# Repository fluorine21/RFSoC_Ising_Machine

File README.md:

# RFSoC_Ising_Machine
An Ising Machine implementation using the RFSoC ZCU1275

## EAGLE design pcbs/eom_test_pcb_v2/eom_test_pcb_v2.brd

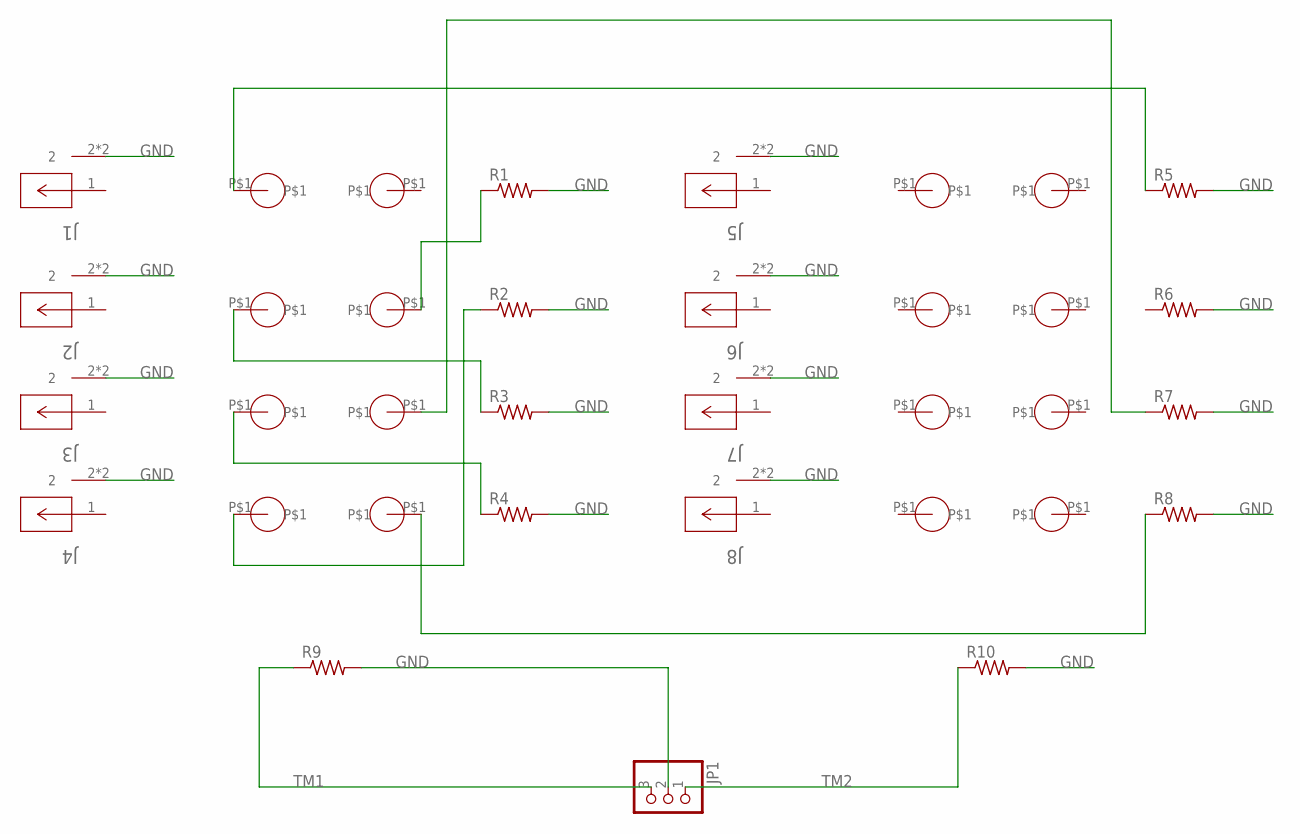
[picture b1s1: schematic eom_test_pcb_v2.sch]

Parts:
J1, J2, J3, J4, J5, J6, J7, J8: 142-0711-821; CONN_142-0711-821_CIN
JP1: PINHD-1X3; 1X03
R1, R2, R3, R4, R5, R6, R7, R8: R-US_M1206; M1206
R9, R10: R-US_R0402; R0402
U$1, U$2, U$3, U$4, U$5, U$6, U$7, U$8, U$9, U$10, U$11, U$12, U$13, U$14, U$15, U$16: SIGNAL_BONDING_DEVICE; SIGNAL_BONDING_PAD

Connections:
GND: J1.2, J1.3 (2), J2.2, J2.3 (2), J3.2, J3.3 (2), J4.2, J4.3 (2), J5.2, J5.3 (2), J6.2, J6.3 (2), J7.2, J7.3 (2), J8.2, J8.3 (2), JP1.2, R1.2, R2.2, R3.2, R4.2, R5.2, R6.2, R7.2, R8.2, R9.2, R10.2
unnamed: R7.1, U$6.P$1
unnamed: R8.1, U$8.P$1
unnamed: R3.1, U$3.P$1
unnamed: R4.1, U$5.P$1
unnamed: R5.1, U$1.P$1
unnamed: R2.1, U$7.P$1
unnamed: R1.1, U$4.P$1
unnamed: R6.1, U$2.P$1
unnamed: J5.1, U$12.P$1
unnamed: J6.1, U$11.P$1
unnamed: J4.1, U$16.P$1
unnamed: J3.1, U$15.P$1
unnamed: J7.1, U$14.P$1
unnamed: J2.1, U$10.P$1
unnamed: J8.1, U$9.P$1
unnamed: J1.1, U$13.P$1
TM1: JP1.3, R9.1
TM2: JP1.1, R10.1

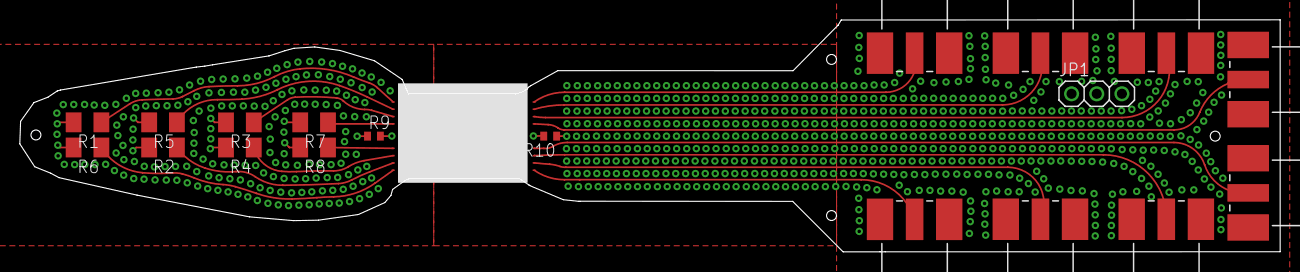
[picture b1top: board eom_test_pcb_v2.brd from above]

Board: 4 copper layers, 127.2 x 23.4 mm, 35 parts (0 on the bottom side), 19 nets.

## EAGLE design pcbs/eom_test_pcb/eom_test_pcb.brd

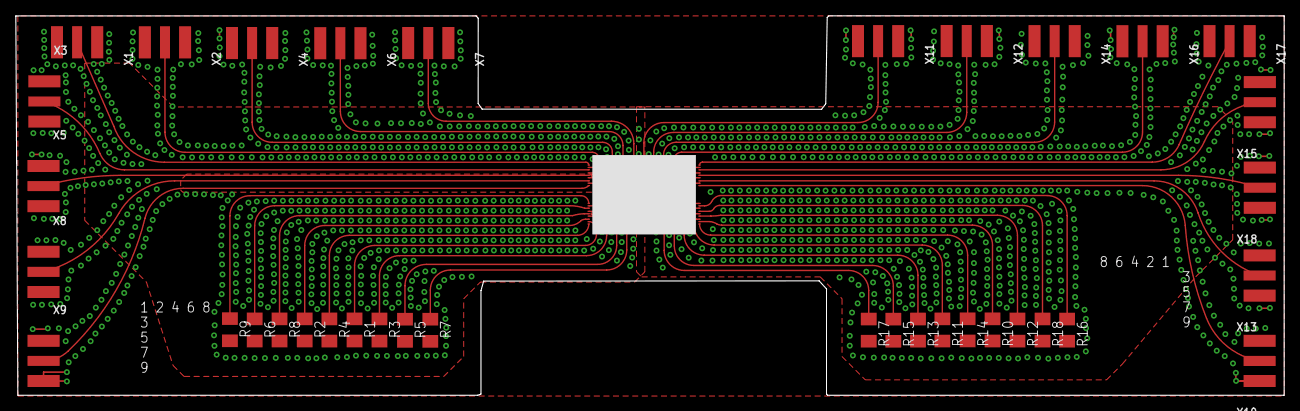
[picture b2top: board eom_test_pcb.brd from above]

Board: 4 copper layers, 160.3 x 47.9 mm, 72 parts (0 on the bottom side), 37 nets.

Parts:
R1, R2, R3, R4, R5, R6, R7, R8, R9, R10, R11, R12, R13, R14, R15, R16, R17, R18: M1206
U$1, U$2, U$3, U$4, U$5, U$6, U$7, U$8, U$9, U$10, U$11, U$12, U$13, U$14, U$15, U$16, U$17, U$18, U$19, U$20, U$21, U$22, U$23, U$24, U$25, U$26, U$27, U$28, U$29, U$30, U$31, U$32, U$33, U$34, U$35, U$36: SIGNAL_BONDING_DEVICE; SIGNAL_BONDING_PAD
X1, X2, X3, X4, X5, X6, X7, X8, X9, X10, X11, X12, X13, X14, X15, X16, X17, X18: SMA_EDGELAUNCH

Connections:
GND: R1.2, R2.2, R3.2, R4.2, R5.2, R6.2, R7.2, R8.2, R9.2, R10.2, R11.2, R12.2, R13.2, R14.2, R15.2, R16.2, R17.2, R18.2, X1.GND@1, X1.GND@2, X1.GND@3, X1.GND@4, X2.GND@1, X2.GND@2, X2.GND@3, X2.GND@4, X3.GND@1, X3.GND@2, X3.GND@3, X3.GND@4, X4.GND@1, X4.GND@2, X4.GND@3, X4.GND@4, X5.GND@1, X5.GND@2, X5.GND@3, X5.GND@4, X6.GND@1, X6.GND@2, X6.GND@3, X6.GND@4, X7.GND@1, X7.GND@2, X7.GND@3, X7.GND@4, X8.GND@1, X8.GND@2, X8.GND@3, X8.GND@4, X9.GND@1, X9.GND@2, X9.GND@3, X9.GND@4, X10.GND@1, X10.GND@2, X10.GND@3, X10.GND@4, X11.GND@1, X11.GND@2, X11.GND@3, X11.GND@4, X12.GND@1, X12.GND@2, X12.GND@3, X12.GND@4, X13.GND@1, X13.GND@2, X13.GND@3, X13.GND@4, X14.GND@1, X14.GND@2, X14.GND@3, X14.GND@4, X15.GND@1, X15.GND@2, X15.GND@3, X15.GND@4, X16.GND@1, X16.GND@2, X16.GND@3, X16.GND@4, X17.GND@1, X17.GND@2, X17.GND@3, X17.GND@4, X18.GND@1, X18.GND@2, X18.GND@3, X18.GND@4
unnamed: U$1.P$1, X1.P
unnamed: R1.1, U$2.P$1
unnamed: U$3.P$1, X2.P
unnamed: R2.1, U$4.P$1
unnamed: U$5.P$1, X3.P
unnamed: R3.1, U$6.P$1
unnamed: U$7.P$1, X4.P
unnamed: R4.1, U$8.P$1
unnamed: U$9.P$1, X5.P
unnamed: R5.1, U$10.P$1
unnamed: U$11.P$1, X6.P
unnamed: R6.1, U$12.P$1
unnamed: U$13.P$1, X7.P
unnamed: R7.1, U$14.P$1
unnamed: U$15.P$1, X8.P
unnamed: R8.1, U$16.P$1
unnamed: U$17.P$1, X9.P
unnamed: R9.1, U$18.P$1
unnamed: U$19.P$1, X10.P
unnamed: R10.1, U$20.P$1
unnamed: U$21.P$1, X11.P
unnamed: R11.1, U$22.P$1
unnamed: U$23.P$1, X12.P
unnamed: R12.1, U$24.P$1
unnamed: U$25.P$1, X13.P
unnamed: R13.1, U$26.P$1
unnamed: U$27.P$1, X14.P
unnamed: R14.1, U$28.P$1
unnamed: U$29.P$1, X15.P
unnamed: R15.1, U$30.P$1
unnamed: U$31.P$1, X16.P
unnamed: R16.1, U$32.P$1
unnamed: U$33.P$1, X17.P
unnamed: R17.1, U$34.P$1
unnamed: U$35.P$1, X18.P
unnamed: R18.1, U$36.P$1

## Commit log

2021-03-31 Added input scaler for ADC and wrote dac driver
2021-04-01 Wrote part of adc driver tb and alg for populating input scaler registers
2021-04-03 Comt before going home on 4 3 2021
2021-04-04 added modelsim project
2021-04-04 Finished test bench for ADC driver
2021-04-06 Added new memory based lookup tables to input and output scalers
2021-04-09 Updated dac and adc drivers
2021-04-10 Finalized layout for adc driver and added dac driver tb
2021-04-11 Fleshed out dac driver
2021-04-11 Saving dac driver again
2021-04-12 Fixed some bugs involving the lookup table
2021-04-19 Pushing to tablet
2021-04-19 Pushing back to lenovo
2021-04-19 Fleshed out experiment fsm and added fsm components for internal delay measurement
2021-04-29 Got everything compiling and fixed DAC output for DC offset
2021-04-29 Did rough implementation of the FSM and wired up the fifos to be on the inside
2021-06-14 Fixed small bug in ADC test bench
2021-06-14 working adc driver test bench
2021-06-16 wrote skeleton of experiment fsm tb and added halt and valid buffer check to fsm
2021-06-16 added more checks to experiment fsm tb
2021-06-23 Added more tests for experiment FSM and added logic to push buffer outputs to module outputs each cycle
2021-06-23 All tests up to delay measurement are working
2021-06-29 push before NL trip
2021-06-30 Final final commit before leaving:
2021-07-10 Finished debugging FSM for all current tests and added error flag
2021-07-11 Started top level design and added gpio readers and writers
2021-07-11 added adc drivers to top level
2021-07-12 Connected up most of the rest of the top level with the fifos
2021-07-13 Started writing tb for top level
2021-07-13 fleshed out most of tb
2021-07-15 Top level tb in a compilable state
2021-07-20 Push back to campus
2021-07-22 Wrote assembler and added NL output for A channel
2021-07-22 Working A and C readback over GPIO
2021-07-28 Added complex number support to the ising package
2021-07-30 Finished writing the model for both chips and wrote the cal alg for the nl chip
2021-08-01 Wrote half of mac cal alg
2021-08-02 Wrote most of mac cal alg
2021-08-02 debuged cmp num implementation, working on debugging nl chip
2021-08-04 NL cal is working, MAC and NL models are both working
2021-08-07 push before reboot
2021-08-10 Finished debugging chip model, looks like add, mul, and nl are all working correctly
2021-08-16 Finished initial routing for EOM PCB
2021-08-17 commit before restart
2021-08-17 commit before going downstairs to meet with Luis
2021-08-20 before adding rest of vias
2021-08-20 board in finished state, sending to PCBWay
2021-08-20 Fixed board to have correct layer thickness
2021-08-23 Push before mitering
2021-08-23 Push after sending to PCBWay in this state
2021-08-24 Started writing full sim tb
2021-08-29 Most of full test bench written
2021-08-30 Added thermals to top pour of eom test pcb and fixed small bug in chip model I introduced during debugging
2021-09-01 Working LUT calibration algorithm for the NL chip
2021-09-01 Fixed NL LUT gen alg to Gordon's liking
2021-09-03 Somewhat working MAC cal algorithm for the ideal case
2021-09-09 Cal for mac seems to be working, writing full sim now
2021-09-09 Dealt with some minor bugs in lookup_table.sv
2021-09-13 Changed out peak detector in adc for sample selector
2021-09-14 Full sim tb in a compilable state
2021-09-14 Ising assembler in a working state
2021-09-15 Added assembler support for variables
2021-09-28 Almost working simulation, del cal works and load program works
2021-10-31 Started working on new rf pcb
2021-11-06 quarter way done with routing
2021-11-10 V2 design finished
2021-11-11 Fixed layer issue
2021-11-12 Removed solder mask from bottom and put sample square on tnames
2021-11-18 Adjusted traces to 6.8mil and fixed DRC complaints
2021-12-16 Added GDS for EOMs
2022-01-10 Added current DC EOM design (EOM4)
2022-02-02 Wrote serial server
2022-02-04 Added test data from DC eom bandwidth measurement:
2022-02-28 Added first RF data
2022-03-05 Added SEM images
2022-03-05 Added new EOM data
2022-03-07 Finished preliminary NL chip design
2022-03-08 Added original DC EOM data
2022-03-09 Added data for device 4-1
2022-03-15 Updated MAC layout
2022-03-17 Added output stuff and path length equalization
2022-03-18 Layout DRC working
2022-03-25 Did more electrical routing for MAC chip
2022-03-25 Finished up electrical connections for MAC chip and migrated it to a py file
2022-03-27 Started dynamic locking
2022-03-27 Added scope scraper script
2022-03-28 Made panelized mac design
2022-03-29 Started circuit design for eom driver
2022-03-29 Finished simulation for output stage of eom driver
2022-03-29 Worked a bit more on the PCB
2022-03-31 Pushing from server
2022-04-02 Finished up initial code for db and made a dent into db_tl
2022-04-02 dl and dl_tb both compile, had to add some extra config reg stuff to dl

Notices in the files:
parts and their libraries:
COPYRIGHT: Copyright (C) 2021 Ultra Librarian. All rights reserved.
